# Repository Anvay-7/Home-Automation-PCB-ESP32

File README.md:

# Home-Automation-PCB-ESP32
For BIT PCB Challenge 2021

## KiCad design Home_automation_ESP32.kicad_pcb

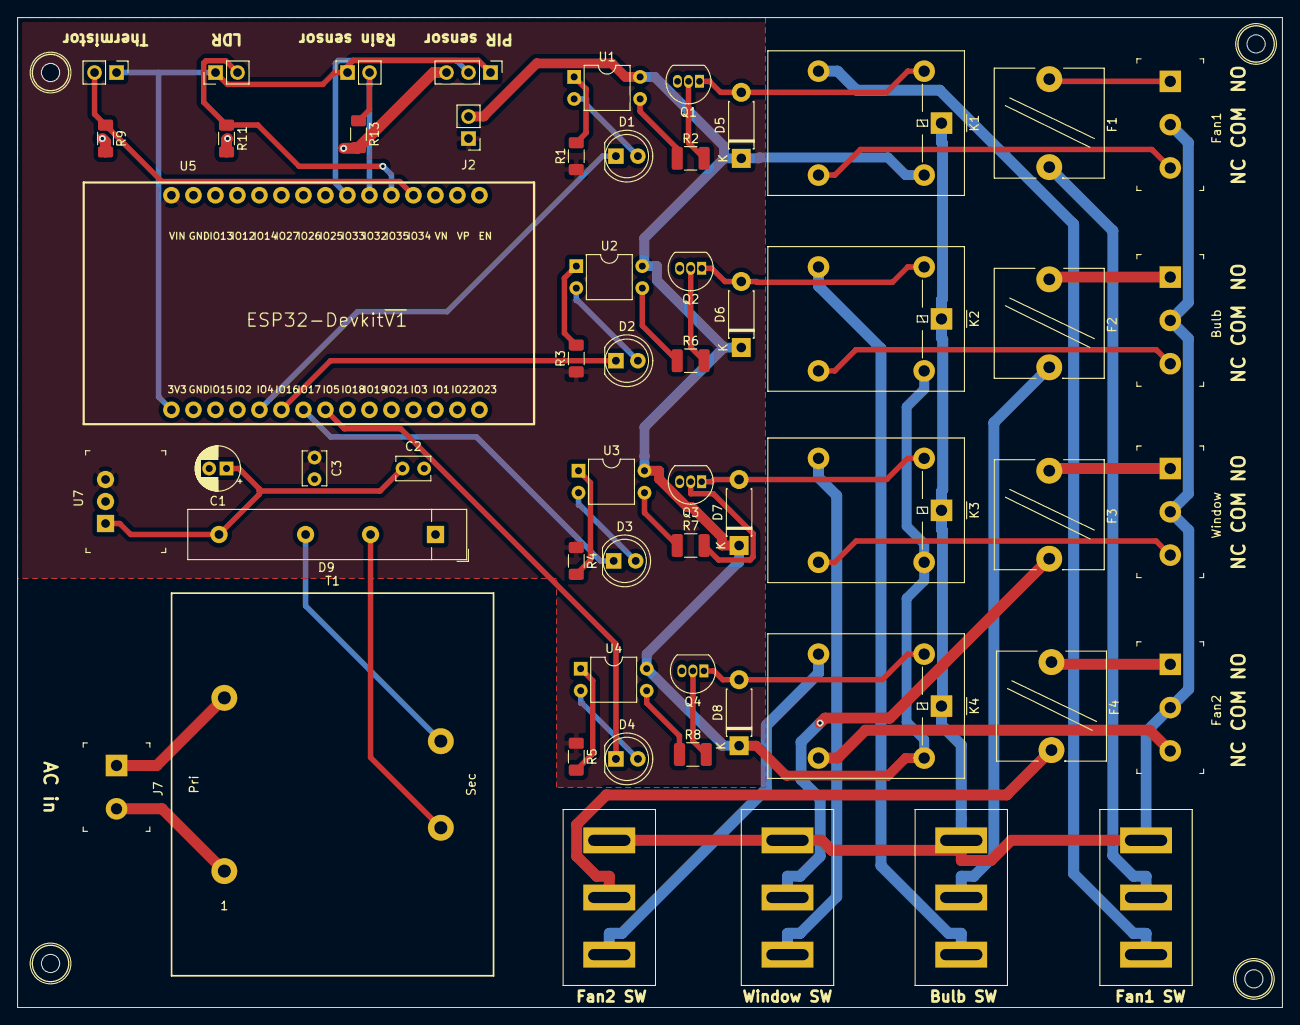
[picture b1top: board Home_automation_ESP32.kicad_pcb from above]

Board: 2 copper layers, 146.1 x 114.3 mm, 56 parts (0 on the bottom side), 54 nets.

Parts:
Bulb: Bulb; Term_Block_1x3_P5mm
Bulb SW: SW_SPDT; rocker_switch
C1: 470uF 50V; CP_Radial_D5.0mm_P2.00mm
C2, C3: 0.01uF; C_Disc_D3.8mm_W2.6mm_P2.50mm
D1, D2, D3, D4: LED; LED_D5.0mm
D5, D6, D7, D8: D; D_DO-41_SOD81_P7.62mm_Horizontal
D9: B250C3x00-2200A; Diode_Bridge_32.0x5.6x17.0mm_P10.0mm_P7.5mm
F1, F2, F3, F4: Fuse; Fuseholder_Cylinder-5x20mm_Bulgin_FX0456_Vertical_Closed
Fan1: Fan1; Term_Block_1x3_P5mm
Fan1 SW, Fan2 SW: SW_SPDT; rocker_switch
Fan2: Fan2; Term_Block_1x3_P5mm
J2: Conn_01x02; PinHeader_1x02_P2.54mm_Vertical
J7: AC_IN; Term_Block_1x2_P5mm
K1, K2, K3, K4: G5LE-1; Relay_SPDT_Omron-G5LE-1
LDR: LDR03; PinHeader_1x02_P2.54mm_Vertical
PIR sensor: AM312; PinHeader_1x03_P2.54mm_Vertical
Q1, Q2, Q3, Q4: BC547; TO-92_Inline
R1, R3, R4, R5: 1k; R_1206_3216Metric_Pad1.30x1.75mm_HandSolder
R2, R6, R7, R8: 510; R_1210_3225Metric_Pad1.30x2.65mm_HandSolder
R9, R11, R13: 10k; R_1206_3216Metric_Pad1.30x1.75mm_HandSolder
Rain sensor: Rain Sensor; PinSocket_1x02_P2.54mm_Vertical
T1: Transformer_1P_1S; Transformer_CHK_EI42-5VA_1xSec
Thermistor: Thermistor; PinHeader_1x02_P2.54mm_Vertical
U1, U2, U3, U4: PC817; DIP-4_W7.62mm
U5: ESP32DEVKITV1; ESP32-DEVKITV1
U7: L7805; 3-SIP_Module_V7805-1000
Window: Window; Term_Block_1x3_P5mm
Window SW: SW_SPDT; rocker_switch

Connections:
/Relay /COM4: Bulb.2, Bulb SW.3, Fan1.2, Fan1 SW.3, Fan2.2, Fan2 SW.3, K1.1, K2.1, K3.1, K4.1, Window.2, Window SW.3
/Relay /NC4: Fan2.3, K4.4
GND: C1.2, C2.2, C3.2, D9.1, PIR sensor.3, Q1.3, Q2.3, Q3.3, Q4.3, R9.2, R11.2, R13.2, U5.2, U7.2
IN1: D1.1, U5.5
IN2: D2.1, U5.6
IN3: D3.1, U5.7
IN4: D4.1, U5.8
JD-VCC: D5.1, D6.1, D7.1, D8.1, J2.2, K1.5, K2.5, K3.5, K4.5, U1.4, U2.4, U3.4, U4.4
unnamed: C1.1, C2.1, D9.4, U7.1
unnamed: D1.2, U1.2
unnamed: D2.2, U2.2
unnamed: D3.2, U3.2
unnamed: D4.2, U4.2
unnamed: D5.2, K1.2, Q1.1
unnamed: D6.2, K2.2, Q2.1
unnamed: D7.2, K3.2, Q3.1
unnamed: D8.2, K4.2, Q4.1
unnamed: D9.2, T1.4
unnamed: D9.3, T1.3
unnamed: F1.1, Fan1.1
unnamed: F1.2, Fan1 SW.2
unnamed: Bulb.1, F2.1
unnamed: Bulb SW.2, F2.2
unnamed: F3.1, Window.1
unnamed: F3.2, Window SW.2
unnamed: F4.1, Fan2.1
unnamed: F4.2, Fan2 SW.2
unnamed: Fan1.3, K1.4
unnamed: K3.4, Window.3
unnamed: Bulb.3, K2.4
unnamed: J7.1, T1.2
unnamed: J7.2, T1.1
unnamed: Fan1 SW.1, K1.3
unnamed: Bulb SW.1, K2.3
unnamed: K3.3, Window SW.1
unnamed: Fan2 SW.1, K4.3
unnamed: Q1.2, R2.2
unnamed: Q2.2, R6.2
unnamed: Q3.2, R7.2
unnamed: Q4.2, R8.2
unnamed: R1.2, U1.1
unnamed: R2.1, U1.3
unnamed: R3.2, U2.1
unnamed: R4.2, U3.1
unnamed: R5.2, U4.1
unnamed: R6.1, U2.3
unnamed: R7.1, U3.3
unnamed: R8.1, U4.3
unnamed: R9.1, Thermistor.2, U5.19
unnamed: LDR.1, PIR sensor.1, Rain sensor.1, Thermistor.1, U5.1
unnamed: LDR.2, R11.1, U5.20
unnamed: R13.1, Rain sensor.2, U5.21
unnamed: PIR sensor.2, U5.22
VCC: C3.1, J2.1, R1.1, R3.1, R4.1, R5.1, U5.30, U7.3
